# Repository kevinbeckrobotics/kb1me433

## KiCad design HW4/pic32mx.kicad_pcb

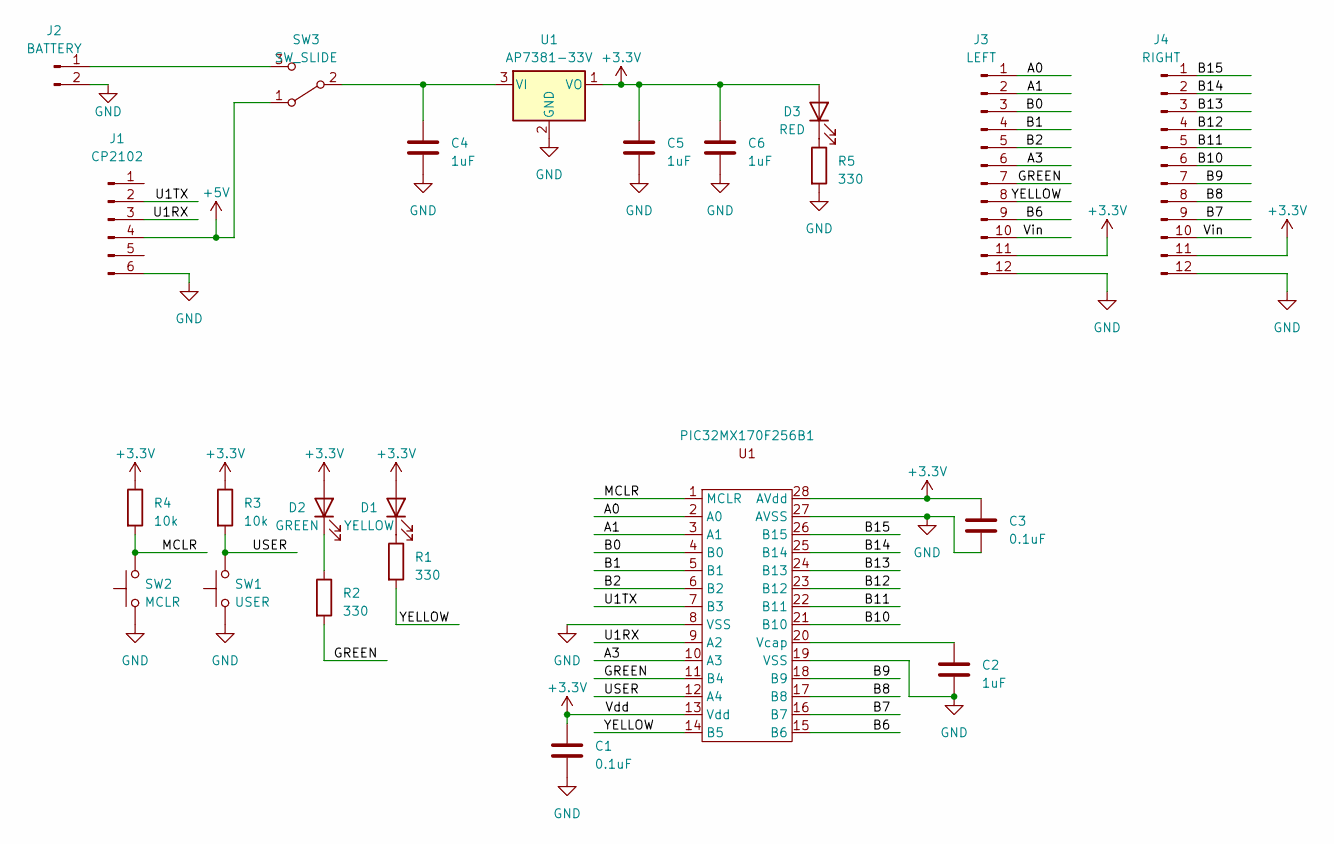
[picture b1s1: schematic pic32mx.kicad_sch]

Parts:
C1, C3: 0.1uF; C_Axial_L3.8mm_D2.6mm_P7.50mm_Horizontal
C2, C4, C5, C6: 1uF; C_Axial_L3.8mm_D2.6mm_P7.50mm_Horizontal
D1: YELLOW; LED_Rectangular_W3.9mm_H1.9mm
D2: GREEN; LED_Rectangular_W3.9mm_H1.9mm
D3: RED; LED_Rectangular_W3.9mm_H1.9mm
J1: CP2102; PinSocket_1x06_P2.54mm_Vertical
J2: BATTERY; PinHeader_1x02_P2.54mm_Vertical
J3: LEFT; PinHeader_1x12_P2.54mm_Vertical
J4: RIGHT; PinHeader_1x12_P2.54mm_Vertical
PIC32MX170F256B1: DIP-28_W7.62mm
R1, R2, R5: 330; R_Axial_DIN0204_L3.6mm_D1.6mm_P7.62mm_Horizontal
R3, R4: 10k; R_Axial_DIN0204_L3.6mm_D1.6mm_P7.62mm_Horizontal
SW1: USER; 2 Pin Button
SW2: MCLR; 2 Pin Button
SW3: SW_SLIDE; PinHeader_1x03_P2.54mm_Vertical
U1: AP7381-33V; TO-92_Inline_Wide

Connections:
+3.3V: C1.1, C3.1, C5.1, C6.1, D1.2 (A), D2.2 (A), D3.2 (A), J3.11, J4.11, PIC32MX170F256B1.13 (Vdd), PIC32MX170F256B1.28 (AVdd), R3.1, R4.1, U1.1 (VO)
+5V: J1.4, SW3.1 (A)
/A0: J3.1, PIC32MX170F256B1.2 (A0)
/A1: J3.2, PIC32MX170F256B1.3 (A1)
/A3: J3.6, PIC32MX170F256B1.10 (A3)
/B0: J3.3, PIC32MX170F256B1.4 (B0)
/B1: J3.4, PIC32MX170F256B1.5 (B1)
/B2: J3.5, PIC32MX170F256B1.6 (B2)
/B6: J3.9, PIC32MX170F256B1.15 (B6)
/B7: J4.9, PIC32MX170F256B1.16 (B7)
/B8: J4.8, PIC32MX170F256B1.17 (B8)
/B9: J4.7, PIC32MX170F256B1.18 (B9)
/B10: J4.6, PIC32MX170F256B1.21 (B10)
/B11: J4.5, PIC32MX170F256B1.22 (B11)
/B12: J4.4, PIC32MX170F256B1.23 (B12)
/B13: J4.3, PIC32MX170F256B1.24 (B13)
/B14: J4.2, PIC32MX170F256B1.25 (B14)
/B15: J4.1, PIC32MX170F256B1.26 (B15)
/GREEN: J3.7, PIC32MX170F256B1.11 (B4), R2.2
/MCLR: PIC32MX170F256B1.1 (MCLR), R4.2, SW2.2
/U1RX: J1.3, PIC32MX170F256B1.9 (A2)
/U1TX: J1.2, PIC32MX170F256B1.7 (B3)
/USER: PIC32MX170F256B1.12 (A4), R3.2, SW1.2
/Vin: J3.10, J4.10
/YELLOW: J3.8, PIC32MX170F256B1.14 (B5), R1.2
GND: C1.2, C2.2, C3.2, C4.2, C5.2, C6.2, J1.6, J2.2, J3.12, J4.12, PIC32MX170F256B1.8 (VSS), PIC32MX170F256B1.19 (VSS), PIC32MX170F256B1.27 (AVSS), R5.2, SW1.1, SW2.1, U1.2 (GND)
unnamed: D1.1 (K), R1.1
unnamed: D2.1 (K), R2.1
unnamed: D3.1 (K), R5.1
unnamed: J2.1, SW3.3 (C)
unnamed: C2.1, PIC32MX170F256B1.20 (Vcap)
unnamed: C4.1, SW3.2 (B), U1.3 (VI)

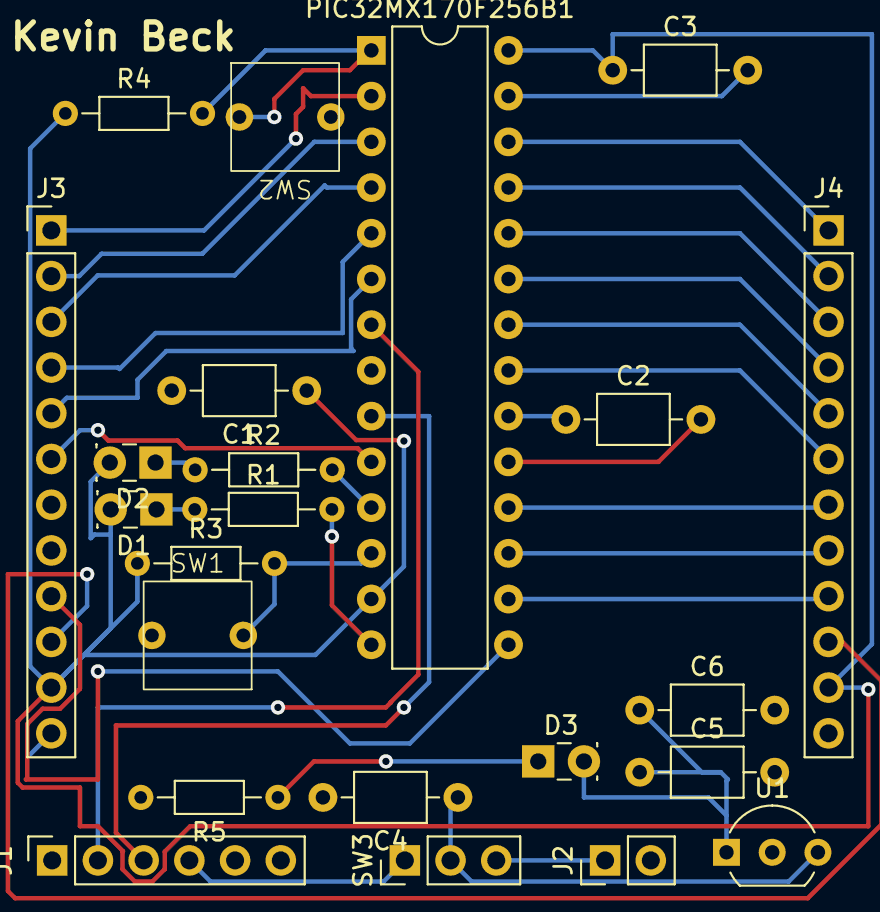
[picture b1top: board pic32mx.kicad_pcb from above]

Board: 2 copper layers, 23 parts (0 on the bottom side), 32 nets.

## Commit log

2023-06-08 Create code.py
    Homework 13 code (didn't work due to webpage issues)
2023-06-08 Create hw14.c
    Servo control
2023-06-08 Create samp
